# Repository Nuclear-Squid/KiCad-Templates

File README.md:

# KiCad-Templates

A Python program to help the conception of PCBs by importing predefined templates, containing standalone electronic functions.

## Why it matters

Some electronic functions may be very common, but hard or time-consuming to implement. For instance, integrating a microcontroller properly means making sure we have :

- good power management (with a strong voltage regulator and efficient bypass capacitors)
- a clean routing (to keep high-speed signals away from each other and maintain a good ground plane)
- a compact design
- easy to access GPIOs

This project aims to aid engineers by easily reuse complex electronic functions to both speed up development, and ensure a high quality design.

## How it works

Each template is defined using KiCad’s “hierarchical sheet” system, which allows the whole template to be placed onto an existing schematic as a sort of dummy component, with all of it’s out-going connection being exported as standard pins, able to be reused in the larger sheet. This allows the engineer to write detailed documentation for each template, without it making the larger project messy.

More information on the schematic side of the project can be found in the `sch_api.md` file.

## Roadmap

For now, only the schematic imports are supported, as the PCB routing seemed to be more challenging : The files are more complex, we need to fix a couple issues detailed in `sch_api.md`, recreate the net list and update some information in the imported PCB files before integrating them into the board.

This is our main long-term objective, and we are actively working on the foundations needed for this feature.

Other (smaller) features we’d like to add are :

- a more straight forward way of creating a new project
- allow the user to define their own templates outside this application
- improve the user interface
- add a KiCad plugin interface, for a seamless integration

# Test cases

## Feature tests

###  Basic project generation

- [x] Can the program generate projects using the subsystem files given?
- [x] Can it handle multiple instances of the same subsystems?
- [ ] Will it work on more than one layer?

### Software maintenance

- [ ] Is the installation process well documented?
- [ ] Is the project supported on every computer?
- [ ] Can the user add new subsystems?

## User tests

- [ ] Installation
- [ ] Generation
- [ ] Addition of new systems

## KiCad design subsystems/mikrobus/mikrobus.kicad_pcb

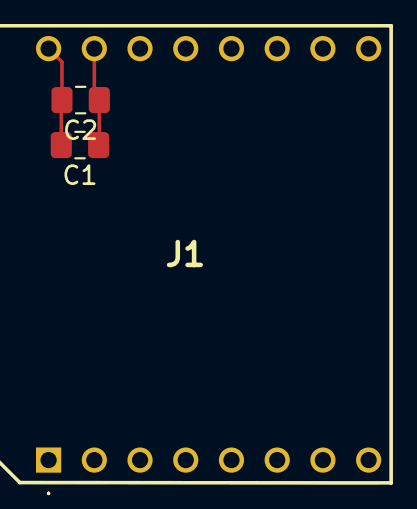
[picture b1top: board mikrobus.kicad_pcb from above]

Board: 2 copper layers, 3 parts (0 on the bottom side), 2 nets.

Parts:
C1: 10u; C_0805_2012Metric_Pad1.18x1.45mm_HandSolder
C2: 100n; C_0805_2012Metric_Pad1.18x1.45mm_HandSolder
J1: MIKROE-4247; MIKROE4247

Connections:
+3V3: C1.1, C2.1, J1.15 (+3.3V)
GND: C1.2, C2.2, J1.1 (GND_1), J1.16 (GND_2)

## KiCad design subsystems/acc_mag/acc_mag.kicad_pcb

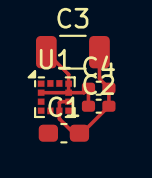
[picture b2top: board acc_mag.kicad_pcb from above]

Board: 2 copper layers, 5 parts (0 on the bottom side), 3 nets.

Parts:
C1: 220nF; C_0603_1608Metric_Pad1.08x0.95mm_HandSolder
C2, C4: 100nF; C_0402_1005Metric_Pad0.74x0.62mm_HandSolder
C3: 10uF; C_1206_3216Metric
U1: LSM303AGRTR; LGA-12_2x2mm_P0.5mm

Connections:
+3V3: C2.1, C3.1, C4.1, U1.2 (CS_XL), U1.3 (CS_MAG), U1.9 (VDD), U1.10 (VDD_IO)
GND: C1.2, C2.2, C3.2, C4.2, U1.6 (GND_1), U1.8 (GND_2)
unnamed: C1.1, U1.5 (C1)

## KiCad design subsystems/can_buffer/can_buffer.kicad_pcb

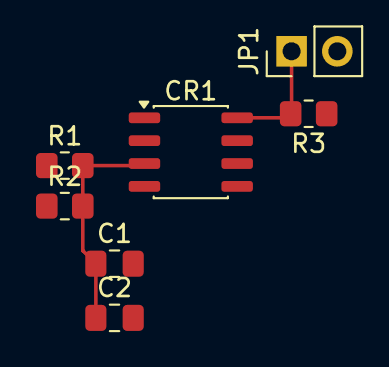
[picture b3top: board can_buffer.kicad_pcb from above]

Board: 2 copper layers, 7 parts (0 on the bottom side), 4 nets.

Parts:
C1: 10u; C_0805_2012Metric_Pad1.18x1.45mm_HandSolder
C2: 100n; C_0805_2012Metric_Pad1.18x1.45mm_HandSolder
CR1: L9616; SO-8_3.9x4.9mm_P1.27mm
JP1: speed_controller; PinHeader_1x02_P2.54mm_Vertical
R1, R2: 0; R_0805_2012Metric_Pad1.20x1.40mm_HandSolder
R3: 4K7; R_0805_2012Metric_Pad1.20x1.40mm_HandSolder

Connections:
+3V3: R1.1, R3.1
GND: C1.2, C2.2, CR1.2 (GND), JP1.2 (B)
unnamed: CR1.8 (ASC), JP1.1 (A), R3.2
unnamed: C1.1, C2.1, CR1.3 (VS), R1.2, R2.2

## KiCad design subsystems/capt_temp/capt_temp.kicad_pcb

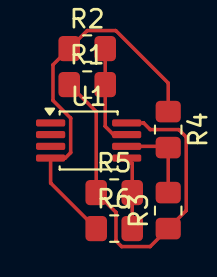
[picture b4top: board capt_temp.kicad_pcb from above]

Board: 2 copper layers, 7 parts (0 on the bottom side), 5 nets.

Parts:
R1, R2, R3, R4, R5, R6: 0; R_0805_2012Metric_Pad1.20x1.40mm_HandSolder
U1: MCP9808_MSOP; MSOP-8_3x3mm_P0.65mm

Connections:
+3V3: R1.1, R3.1, R5.1, U1.8 (V_{DD})
GND: R2.1, R4.1, R6.1, U1.4 (GND)
unnamed: R1.2, R2.2, U1.7 (A0)
unnamed: R3.2, R4.2, U1.6 (A1)
unnamed: R5.2, R6.2, U1.5 (A2)

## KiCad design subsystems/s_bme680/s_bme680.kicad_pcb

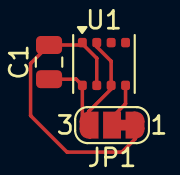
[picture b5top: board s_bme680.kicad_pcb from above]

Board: 2 copper layers, 3 parts (0 on the bottom side), 3 nets.

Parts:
C1: 0.1u; C_0805_2012Metric
JP1: ADDR; SolderJumper-3_P1.3mm_Bridged12_RoundedPad1.0x1.5mm_NumberL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
U1: BME680; Bosch_LGA-8_3x3mm_P0.8mm_ClockwisePinNumbering

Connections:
+3V3: C1.1, JP1.3 (B), U1.2 (CSB), U1.6 (VDDIO), U1.8 (VDD)
GND: C1.2, JP1.1 (A), U1.1 (GND), U1.7 (GND)
unnamed: JP1.2 (C), U1.5 (SDO)

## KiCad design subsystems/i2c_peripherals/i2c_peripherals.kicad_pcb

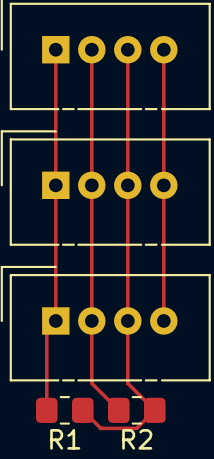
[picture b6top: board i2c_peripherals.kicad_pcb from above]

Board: 2 copper layers, 5 parts (0 on the bottom side), 4 nets.

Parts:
J1, J2, J3: I2C_Grove; NS-Tech_Grove_1x04_P2mm_Vertical
R1, R2: 4K7; R_0805_2012Metric_Pad1.20x1.40mm_HandSolder

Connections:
+3V3: J1.3, J2.3, J3.3, R1.1, R2.1
/SCL: J1.1, J2.1, J3.1, R1.2
/SDA: J1.2, J2.2, J3.2, R2.2
GND: J1.4, J2.4, J3.4

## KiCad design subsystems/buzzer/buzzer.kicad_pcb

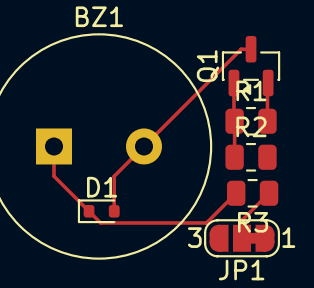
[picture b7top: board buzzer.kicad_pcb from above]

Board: 2 copper layers, 7 parts (0 on the bottom side), 5 nets.

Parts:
BZ1: Buzzer; Buzzer_TDK_PS1240P02BT_D12.2mm_H6.5mm
D1: 1N4148WT; D_SOD-523
JP1: Buzz pwr; SolderJumper-3_P1.3mm_Bridged12_RoundedPad1.0x1.5mm_NumberL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
Q1: MMBT2222A; SOT-23
R1: 10k; R_0805_2012Metric
R2: 1K; R_0805_2012Metric
R3: DNP; R_0805_2012Metric

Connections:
GND: Q1.2 (E), R1.2
unnamed: BZ1.1 (+), D1.1 (K), R3.2
unnamed: BZ1.2 (-), D1.2 (A), Q1.3 (C)
unnamed: JP1.2 (C), R3.1
unnamed: Q1.1 (B), R1.1, R2.1

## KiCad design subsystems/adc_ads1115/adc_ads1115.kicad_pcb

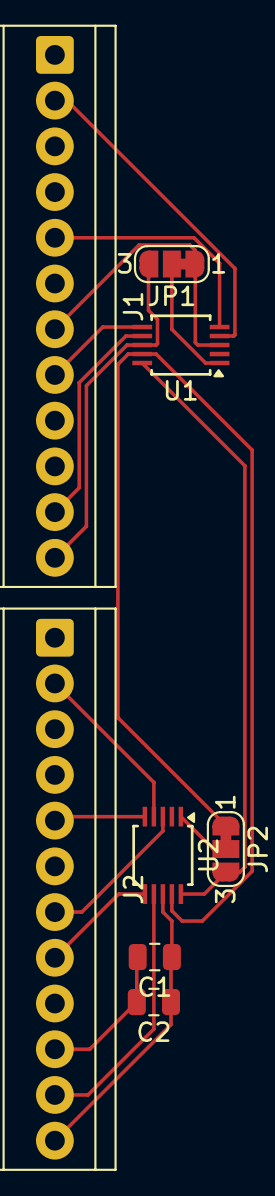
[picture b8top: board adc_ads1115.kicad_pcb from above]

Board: 2 copper layers, 8 parts (0 on the bottom side), 14 nets.

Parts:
C1, C2: 0.1u; C_0805_2012Metric
J1, J2: Conn_01x12; TerminalBlock_TE_1-282834-2_1x12_P2.54mm_Horizontal
JP1, JP2: ADDR; SolderJumper-3_P1.3mm_Bridged12_RoundedPad1.0x1.5mm_NumberL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
U1, U2: ADS1115IDGS; TSSOP-10_3x3mm_P0.5mm

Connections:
+3.3V: C1.1, C2.1, J1.3, J1.6, J1.9, J1.12, J2.3, J2.6, J2.9, J2.12, JP1.3 (B), U1.8 (VDD), U2.8 (VDD)
/SCL: JP2.3 (B), U1.10 (SCL), U2.10 (SCL)
/SDA: JP2.1 (A), U1.9 (SDA), U2.9 (SDA)
GND: C1.2, C2.2, J1.1, J1.4, J1.7, J1.10, J2.1, J2.4, J2.7, J2.10, JP1.1 (A), U1.3 (GND), U2.3 (GND)
unnamed: J1.2, U1.4 (AIN0)
unnamed: J1.5, U1.5 (AIN1)
unnamed: J1.8, U1.6 (AIN2)
unnamed: J1.11, U1.7 (AIN3)
unnamed: J2.2, U2.4 (AIN0)
unnamed: J2.5, U2.5 (AIN1)
unnamed: J2.8, U2.6 (AIN2)
unnamed: J2.11, U2.7 (AIN3)
unnamed: JP1.2 (C), U1.1 (ADDR)
unnamed: JP2.2 (C), U2.1 (ADDR)

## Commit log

2025-10-12 Added a very basic Fix Flake.
2025-10-12 Added a basic uv + ruff setup.
2025-10-12 Added a CI on pushes and pull requests.
2025-10-12 Improved ci: `ruff format` + `ty check`, closes #1.
2025-10-12 Fix errors reported by `ty`.
2025-10-12 oops
2025-10-12 Improved ci: `ruff format` + `ty check`, closes #1. (#2)
    * Improved ci: `ruff format` + `ty check`, closes #1.
    * Fix errors reported by `ty`.
    * oops
2025-10-12 oops, again
2025-10-12 Fixed dummy formatting error.
2025-10-12 Fix code formatter check in ci (#3)
    * oops, again
    * Fixed dummy formatting error.
2025-10-16 PBS and WBS added to a documentation folder
2025-11-06 PBS and WBS added to a documentation folder (#13)
2025-11-06 Added a simple KiCad parser.
2025-11-06 Added a simple KiCad parser. (#15)
2025-11-06 Modular archiecture.
2025-11-20 LLM code working. Hierarchical sheets can be placed as well as simple components. Wires haven't been validated
2025-11-20 CI work
2025-11-20 Ci work again
2025-11-20 Formated
2025-12-11 Auto placement and netlists to pin binding
2026-01-15 MD to update the client. Minor adjusts to api and new templates
2026-01-22 Temporarilly remove CI, doesn’t work the same locally.
2026-01-22 Added KiCad to the nix flake.
2026-01-22 Schematic api progress documented
2026-01-22 Schematic api (#20)
    * LLM code working. Hierarchical sheets can be placed as well as simple components. Wires haven't been validated
    * CI work
    * Ci work again
    * Formated
    * Auto placement and netlists to pin binding
    * MD to update the client. Minor adjusts to api and new templates
2026-01-22 i2c components
2026-01-22 Update readme file to explain the project and reflect it’s current status.
2026-01-22 Update readme file to explain the project and reflect it’s current status. (#21)
2026-01-22 One more mikrobus configuration, adc_ads1115 and buzzer
2026-02-05 Fixed typo in file name.
2026-02-12 Simple CLI interface using the 'click' library.
2026-02-12 Simple CLI interface using the 'click' library. (#22)
2026-02-23 Example fp-lib-table and sym-lib-talbe usage. Project files are being automatically generated but the code has to be clean
2026-02-23 path to the templates fixed
2026-02-23 Lib Files are being copied alongside the new program. Everything was implemented minding the adresses.
2026-02-23 Files organized and project generator translated into a terminal application
2026-02-23 removed testproject
2026-02-23 Schematic templates (#23)
    * One more mikrobus configuration, adc_ads1115 and buzzer
    * Example fp-lib-table and sym-lib-talbe usage. Project files are being automatically generated but the code has to be clean
    * path to the templates fixed
    * Lib Files are being copied alongside the new program. Everything was implemented minding the adresses.
    * Files organized and project generator translated into a terminal application
    * removed testproject
2026-02-23 Yaml metadata + CLI project creation.
2026-02-23 Yaml metadata + CLI project creation. (#24)
    * wip
    * Yaml metadata + CLI project creation.
2026-02-23 Fix hierarchical sheets path.
2026-02-26 Copy the schematic files into the newly created project.
2026-02-26 Removed dummy test project (+ gitignore)
2026-02-26 Mikrobus bug fix. fp and sym lib table address changes
2026-02-26 Readme updated (progress)
2026-03-02 Group pcb items per template.
2026-03-02 Basic pcb inclusion.
2026-03-02 temporary pcb files added to adc, buzzer, i2c and mikrobus
2026-03-02 temporary pcb files for acc_mag, can_buffer, capt_temp, and s_bme680
2026-03-02 Refactor: project creation.
2026-03-02 Abstraction over S-expressions.
2026-03-02 Update KiCad.
2026-03-02 Better project initialization / management.
2026-03-02 Update gitignore
2026-03-05 Quick cleanup
2026-03-05 piece of software used to move pcb whole sections and get their limits based on F_crtyrd
2026-03-09 Pcb (#25)
    * Basic pcb inclusion.
    * Group pcb items per template.
    * piece of software used to move pcb whole sections and get their limits based on F_crtyrd
    ---------
2026-03-09 Automatic pcb placement!
2026-03-12 More yaml updates. Pcb files referenced
2026-03-12 remove unused file
2026-03-16 Netlist problem fix
2026-03-19 Simpler pin placement.
2026-03-19 Integrated changes with existing Schematic imports.
2026-03-19 Wip: cleanup `add_hierarchical_sheet` method.
2026-03-19 Iterate on sexpdata children
2026-03-19 Better metadata description
2026-03-19 Quick fixes: uuid & hierarchical pin placement.
2026-03-19 Finished refactoring the `add_hierarchical_sheet` method.
2026-03-19 Popped up some files from unnecessary submodule.
2026-03-19 More compact pin placement.
2026-03-19 Better project kickstart / template lookup.
2026-03-19 Cleaner cli.
2026-03-19 quick fix after rebase
2026-03-19 Pcb (#26)
    * Basic pcb inclusion.
    * Group pcb items per template.
    * piece of software used to move pcb whole sections and get their limits based on F_crtyrd
    * Automatic pcb placement!
    * More yaml updates. Pcb files referenced
    * remove unused file
2026-03-19 Test section added to readme
2026-03-19 changes to readme. Test list
2026-03-19 Minor bug fux. Quote missing
2026-03-23 Integrated pcb changes (missing net reassignment)
2026-03-26 Fixed annotations (further refactor needed)
2026-03-26 Cleanup
